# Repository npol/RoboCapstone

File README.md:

# RoboCapstone
An autonomous weed eliminating robot

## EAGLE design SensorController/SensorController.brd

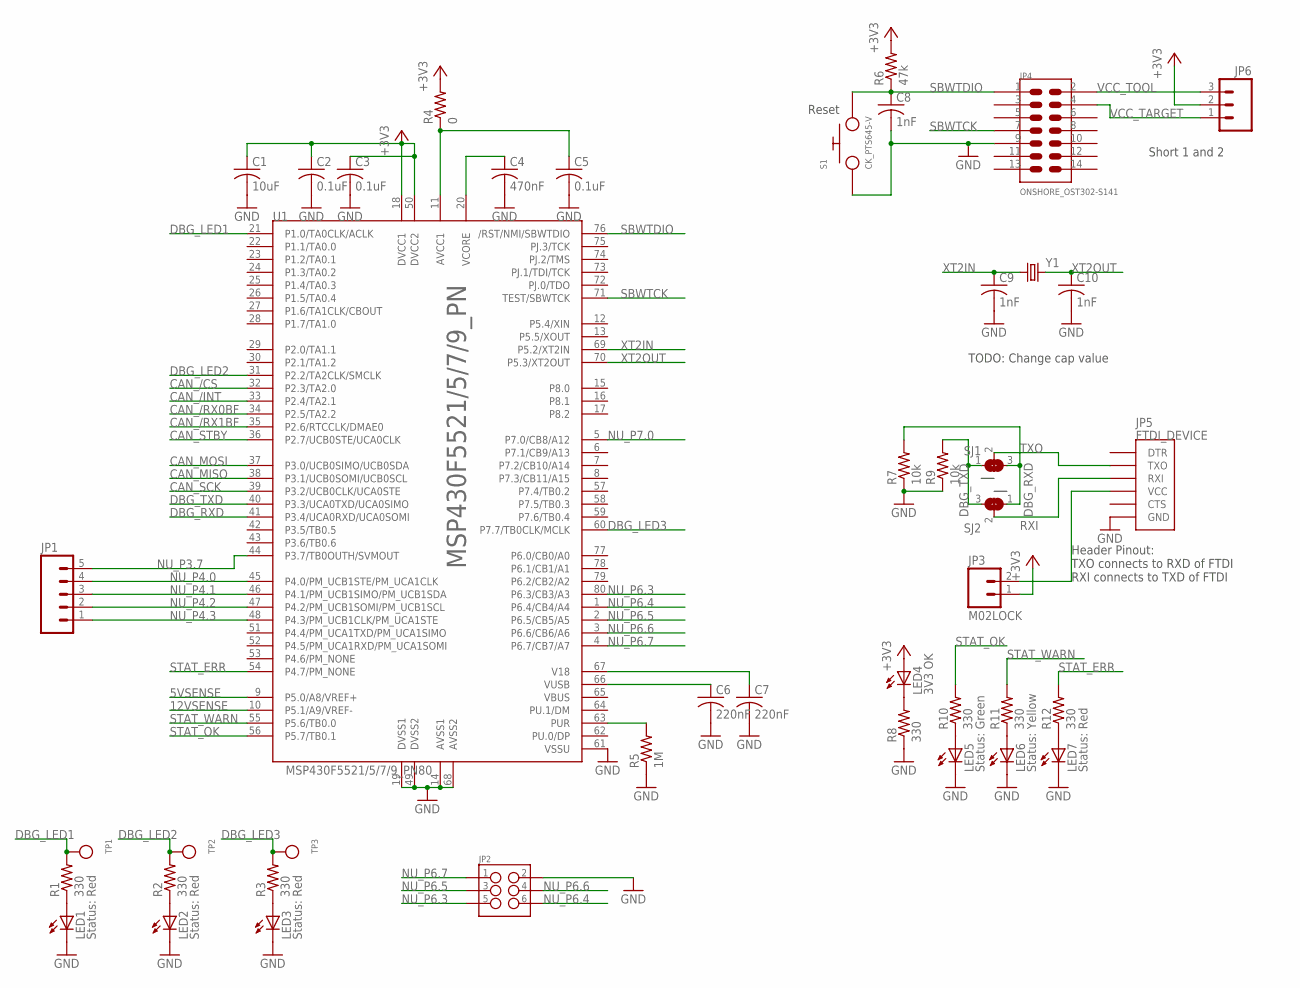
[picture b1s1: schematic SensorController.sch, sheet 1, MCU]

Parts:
C1: 10uF; C0805
C2, C3, C5: 0.1uF; C0603
C4: 470nF; C0603
C6, C7: 220nF; C0603
C8, C9, C10: 1nF; C0603
JP1: M05PTH; 1X05
JP2: M03X22X3_SILK_SM; 2X3
JP3: M02LOCK; 1X02_LOCK
JP4: ONSHORE_OST302-S141
JP5: FTDI_DEVICE; FTDI_DEVICE_SIDE
JP6: M03LOCK; 1X03_LOCK
LED1, LED2, LED3, LED7: Status: Red; LED-0603
LED4: 3V3 OK; LED-0603
LED5: Status: Green; LED-0603
LED6: Status: Yellow; LED-0603
R1, R2, R3, R8, R10, R11, R12: 330; R0603
R4: 0; R0603
R5: 1M; R0603
R6: 47k; R0603
R7, R9: 10k; R0603
S1: CK_PTS645-V
SJ1, SJ2: SOLDERJUMPER_2WAY0603; SOLDERJUMPER_2WAY_OPEN_0603
TP1, TP2, TP3: TESTPOINT0.1"; 1X01_ROUND
U1: MSP430F5521/5/7/9_PN80; PN80
Y1: CRYSTALHC49UV; HC49U-V

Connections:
5VSENSE: U1.9 (P5.0/A8/VREF+); also elsewhere on the board
12VSENSE: U1.10 (P5.1/A9/VREF-); also elsewhere on the board
+3V3: C1.1, C2.1, C3.1, JP3.1, JP6.2, LED4.A, R4.2, R6.2, U1.18 (DVCC1), U1.50 (DVCC2); also elsewhere on the board
AVCC: C5.1, R4.1, U1.11 (AVCC1)
CAN_/CS: U1.32 (P2.3/TA2.0); also elsewhere on the board
CAN_/INT: U1.33 (P2.4/TA2.1); also elsewhere on the board
CAN_/RX0BF: U1.34 (P2.5/TA2.2); also elsewhere on the board
CAN_/RX1BF: U1.35 (P2.6/RTCCLK/DMAE0); also elsewhere on the board
CAN_MISO: U1.38 (P3.1/UCB0SOMI/UCB0SCL); also elsewhere on the board
CAN_MOSI: U1.37 (P3.0/UCB0SIMO/UCB0SDA); also elsewhere on the board
CAN_SCK: U1.39 (P3.2/UCB0CLK/UCA0STE); also elsewhere on the board
CAN_STBY: U1.36 (P2.7/UCB0STE/UCA0CLK); also elsewhere on the board
DBG_LED1: R1.2, TP1.1, U1.21 (P1.0/TA0CLK/ACLK)
DBG_LED2: R2.2, TP2.1, U1.31 (P2.2/TA2CLK/SMCLK)
DBG_LED3: R3.2, TP3.1, U1.60 (P7.7/TB0CLK/MCLK)
DBG_RXD: R7.2, SJ1.3, SJ2.1, U1.41 (P3.4/UCA0RXD/UCA0SOMI)
DBG_TXD: R9.2, SJ1.1, SJ2.3, U1.40 (P3.3/UCA0TXD/UCA0SIMO)
GND: C1.2, C2.2, C3.2, C4.2, C5.2, C6.2, C7.2, C8.2, C9.2, C10.2, JP2.2, JP4.9, JP5.P$6 (GND), LED1.C, LED2.C, LED3.C, LED5.C, LED6.C, LED7.C, R5.1, R7.1, R8.1, R9.1, S1.1, U1.14 (AVSS1), U1.19 (DVSS1), U1.49 (DVSS2), U1.61 (VSSU), U1.68 (AVSS2); also elsewhere on the board
unnamed: JP3.2, JP5.P$4 (VCC)
unnamed: LED4.C, R8.2
unnamed: LED5.A, R10.1
unnamed: LED6.A, R11.1
unnamed: LED7.A, R12.1
unnamed: LED1.A, R1.1
unnamed: R5.2, U1.63 (PUR)
unnamed: LED2.A, R2.1
unnamed: LED3.A, R3.1
NU_P3.7: JP1.5, U1.44 (P3.7/TB0OUTH/SVMOUT)
NU_P4.0: JP1.4, U1.45 (P4.0/PM_UCB1STE/PM_UCA1CLK)
NU_P4.1: JP1.3, U1.46 (P4.1/PM_UCB1SIMO/PM_UCB1SDA)
NU_P4.2: JP1.2, U1.47 (P4.2/PM_UCB1SOMI/PM_UCB1SCL)
NU_P4.3: JP1.1, U1.48 (P4.3/PM_UCB1CLK/PM_UCA1STE)
NU_P6.3: JP2.5, U1.80 (P6.3/CB3/A3)
NU_P6.4: JP2.6, U1.1 (P6.4/CB4/A4)
NU_P6.5: JP2.3, U1.2 (P6.5/CB5/A5)
NU_P6.6: JP2.4, U1.3 (P6.6/CB6/A6)
NU_P6.7: JP2.1, U1.4 (P6.7/CB7/A7)
NU_P7.0: U1.5 (P7.0/CB8/A12)
RXI: JP5.P$3 (RXI), SJ2.2
SBWTCK: JP4.7, U1.71 (TEST/SBWTCK)
SBWTDIO: C8.1, JP4.1, R6.1, S1.2, U1.76 (/RST/NMI/SBWTDIO)
STAT_ERR: R12.2, U1.54 (P4.7/PM_NONE)
STAT_OK: R10.2, U1.56 (P5.7/TB0.1)
STAT_WARN: R11.2, U1.55 (P5.6/TB0.0)
TXO: JP5.P$2 (TXO), SJ1.2
V18: C7.1, U1.67 (V18)
VCC_TARGET: JP4.4, JP6.1
VCC_TOOL: JP4.2, JP6.3
VCORE: C4.1, U1.20 (VCORE)
VUSB: C6.1, U1.66 (VUSB)
XT2IN: C9.1, U1.69 (P5.2/XT2IN), Y1.1
XT2OUT: C10.1, U1.70 (P5.3/XT2OUT), Y1.2

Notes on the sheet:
Short 1 and 2
Reset
TODO: Change cap value
Header Pinout: TXO connects to RXD of FTDI RXI connects to TXD of FTDI

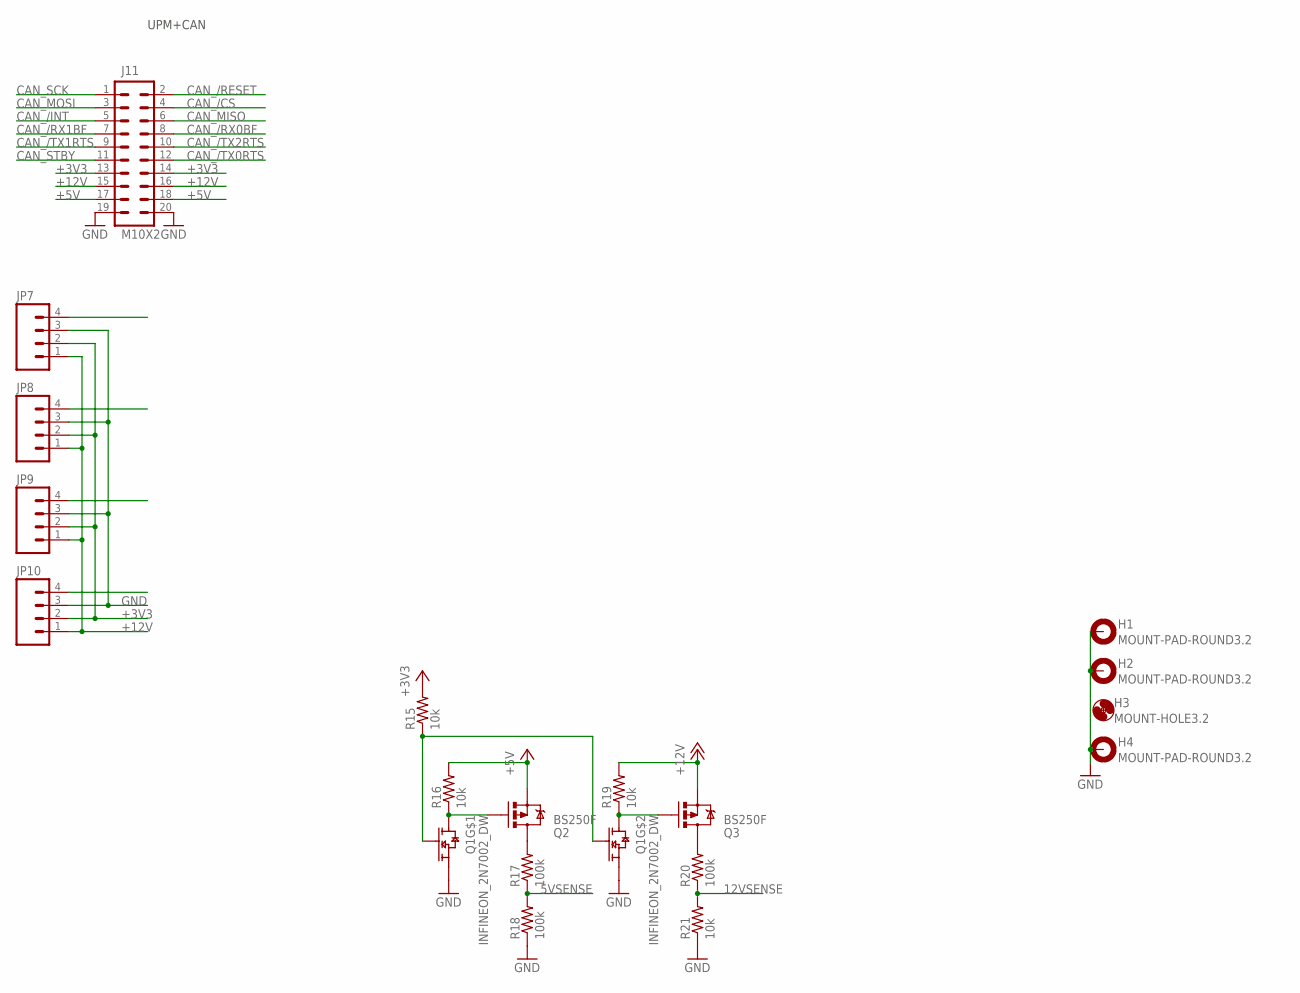
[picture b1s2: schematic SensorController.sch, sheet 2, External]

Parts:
H1, H2, H4: MOUNT-PAD-ROUND3.2; 3,2-PAD
H3: MOUNT-HOLE3.2; 3,2
J11: M10X2; 2X10
JP7, JP8, JP9, JP10: M04PTH; 1X04
Q1: INFINEON_2N7002_DW; INFINEON_SOT363
Q2, Q3: BS250F; SOT23-3
R15, R16, R19, R21: 10k; R0603
R17, R18, R20: 100k; R0603

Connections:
5VSENSE: R17.1, R18.2; also elsewhere on the board
12VSENSE: R20.1, R21.2; also elsewhere on the board
+3V3: J11.13, J11.14, JP7.2, JP8.2, JP9.2, JP10.2, R15.2; also elsewhere on the board
+5V: J11.17, J11.18, Q2.2 (S), R16.2
+12V: J11.15, J11.16, JP7.1, JP8.1, JP9.1, JP10.1, Q3.2 (S), R19.2
CAN_/CS: J11.4; also elsewhere on the board
CAN_/INT: J11.5; also elsewhere on the board
CAN_/RESET: J11.2
CAN_/RX0BF: J11.8; also elsewhere on the board
CAN_/RX1BF: J11.7; also elsewhere on the board
CAN_/TX0RTS: J11.12
CAN_/TX1RTS: J11.9
CAN_/TX2RTS: J11.10
CAN_MISO: J11.6; also elsewhere on the board
CAN_MOSI: J11.3; also elsewhere on the board
CAN_SCK: J11.1; also elsewhere on the board
CAN_STBY: J11.11; also elsewhere on the board
GND: H1.B3,2, H2.B3,2, H4.B3,2, J11.19, J11.20, JP7.3, JP8.3, JP9.3, JP10.3, Q1.1 (SOURCE), Q1.4 (SOURCE), R18.1, R21.1; also elsewhere on the board
unnamed: Q2.3 (D), R17.2
unnamed: Q1.6 (DRAIN), Q2.1 (G), R16.1
unnamed: Q3.3 (D), R20.2
unnamed: Q1.2 (GATE), Q1.5 (GATE), R15.1
VTAP_EN: Q1.3 (DRAIN), Q3.1 (G), R19.1

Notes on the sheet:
UPM+CAN

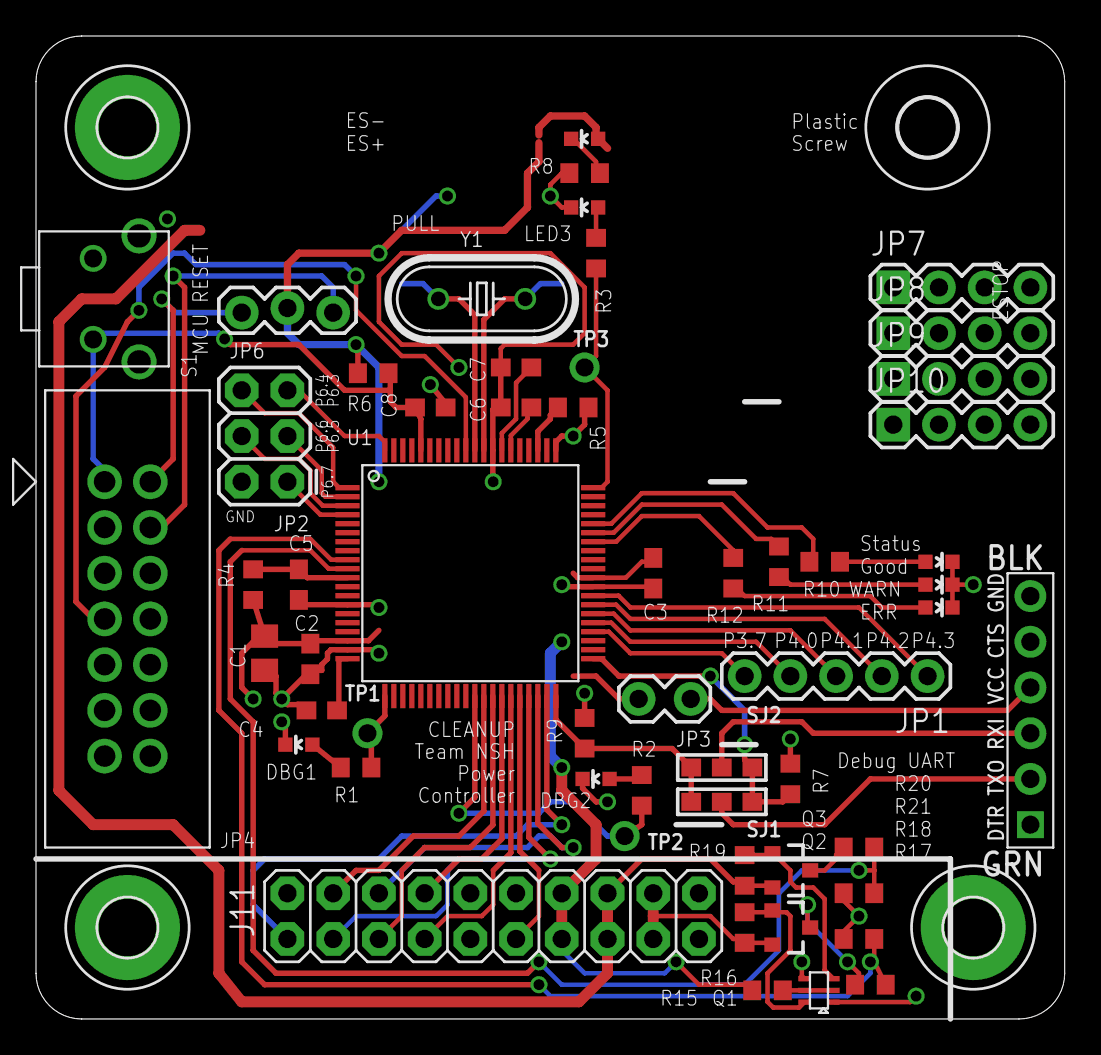
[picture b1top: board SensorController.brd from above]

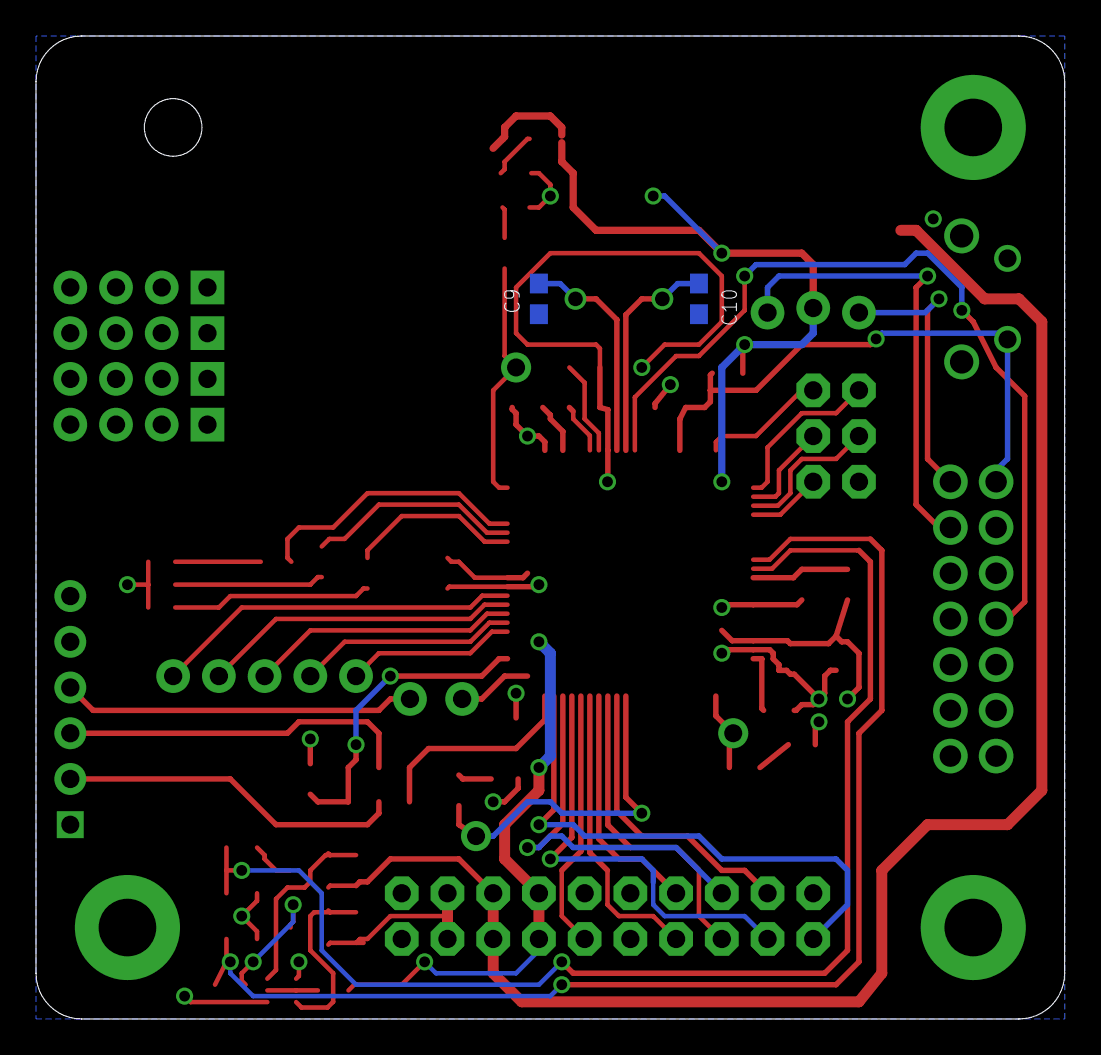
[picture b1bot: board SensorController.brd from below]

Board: 2 copper layers, 57.1 x 54.6 mm, 62 parts (2 on the bottom side), 58 nets.

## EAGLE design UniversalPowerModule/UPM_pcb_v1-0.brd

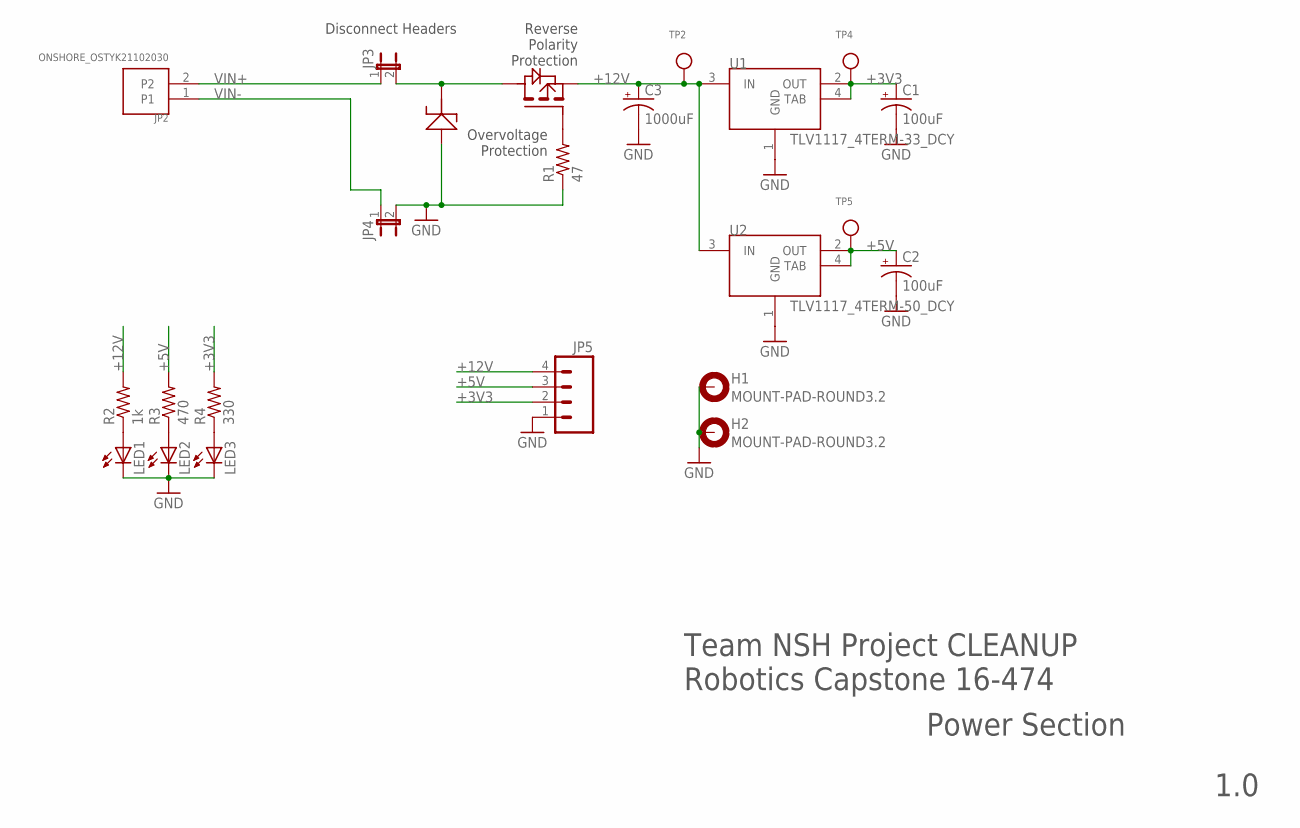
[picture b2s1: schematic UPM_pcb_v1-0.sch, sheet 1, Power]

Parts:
C1, C2: 100uF; E2,5-5
C3: 1000uF; E5-13
D1: VISHAY_SMA6F; VSHY_DO-221AC
H1, H2: MOUNT-PAD-ROUND3.2; 3,2-PAD
JP2: ONSHORE_OSTYK21102030
JP3, JP4: JUMPER2
JP5: M04LOCK; 1X04_LOCK
LED1, LED2, LED3: LED0603; LED-0603
Q1: DMP4047SK3; DIODES_TO252
R1: 47; R0603
R2: 1k; R0603
R3: 470; R0603
R4: 330; R0603
TP2, TP4, TP5: TESTPOINT0.1"; 1X01_ROUND
U1: TLV1117_4TERM-33_DCY; TI_SOT-223_DCY_R-PDSO-G4
U2: TLV1117_4TERM-50_DCY; TI_SOT-223_DCY_R-PDSO-G4

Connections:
+3V3: C1.+, JP5.2, R4.2, TP4.1, U1.2 (OUT), U1.4 (TAB); also elsewhere on the board
+5V: C2.+, JP5.3, R3.2, TP5.1, U2.2 (OUT), U2.4 (TAB); also elsewhere on the board
+12V: C3.+, JP5.4, Q1.2 (S), R2.2, TP2.1, U1.3 (IN), U2.3 (IN); also elsewhere on the board
GND: C1.-, C2.-, C3.-, D1.A, H1.B3,2, H2.B3,2, JP4.2, JP5.1, LED1.C, LED2.C, LED3.C, R1.1, U1.1 (GND), U2.1 (GND); also elsewhere on the board
unnamed: Q1.1 (G), R1.2
unnamed: D1.K, JP3.2, Q1.3 (D)
unnamed: LED1.A, R2.1
unnamed: LED2.A, R3.1
unnamed: LED3.A, R4.1
VIN+: JP2.2, JP3.1
VIN-: JP2.1, JP4.1

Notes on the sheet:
Team NSH Project CLEANUP Robotics Capstone 16-474
1.0
Disconnect Headers
Overvoltage Protection
Reverse Polarity Protection
Power Section

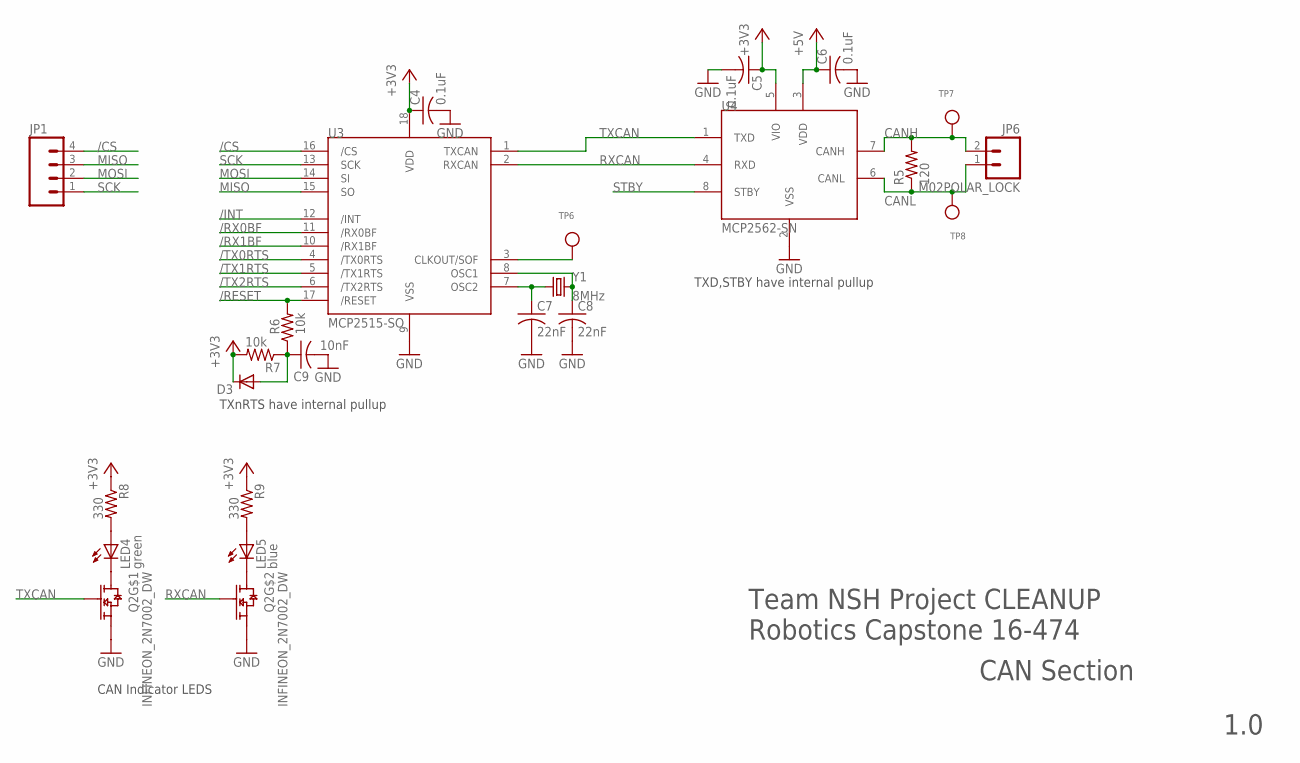
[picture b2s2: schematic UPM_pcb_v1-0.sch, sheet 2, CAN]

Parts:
C4, C5, C6: 0.1uF; C0603
C7, C8: 22nF; C0603
C9: 10nF; C0603
D3: DIODE1N4148; DIODE-1N4148
JP1: M04LOCK; 1X04_LOCK
JP6: M02POLAR_LOCK; MOLEX-1X2_LOCK
LED4: green; LED-0603
LED5: blue; LED-0603
Q2: INFINEON_2N7002_DW; INFINEON_SOT363
R5: 120; R0603
R6, R7: 10k; R0603
R8, R9: 330; R0603
TP6, TP7, TP8: TESTPOINT0.1"; 1X01_ROUND
U3: MCP2515-SO; MCP_SO_SOIC-18
U4: MCP2562-SN; MCP_SN_SOIC-8
Y1: 8MHz; HC49U-V

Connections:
+3V3: C4.1, C5.1, D3.C, R7.2, R8.1, R9.1, U3.18 (VDD), U4.5 (VIO); also elsewhere on the board
+5V: C6.1, U4.3 (VDD); also elsewhere on the board
/CS: JP1.4, U3.16 (/CS); also elsewhere on the board
/INT: U3.12 (/INT); also elsewhere on the board
/RESET: R6.2, U3.17 (/RESET); also elsewhere on the board
/RX0BF: U3.11 (/RX0BF); also elsewhere on the board
/RX1BF: U3.10 (/RX1BF); also elsewhere on the board
/TX0RTS: U3.4 (/TX0RTS); also elsewhere on the board
/TX1RTS: U3.5 (/TX1RTS); also elsewhere on the board
/TX2RTS: U3.6 (/TX2RTS); also elsewhere on the board
CANH: JP6.2, R5.2, TP7.1, U4.7 (CANH)
CANL: JP6.1, R5.1, TP8.1, U4.6 (CANL)
CLKOUT: TP6.1, U3.3 (CLKOUT/SOF)
GND: C4.2, C5.2, C6.2, C7.2, C8.2, C9.2, Q2.1 (SOURCE), Q2.4 (SOURCE), U3.9 (VSS), U4.2 (VSS); also elsewhere on the board
MISO: JP1.3, U3.15 (SO); also elsewhere on the board
MOSI: JP1.2, U3.14 (SI); also elsewhere on the board
unnamed: LED4.C, Q2.6 (DRAIN)
unnamed: C9.1, D3.A, R6.1, R7.1
unnamed: LED5.C, Q2.3 (DRAIN)
unnamed: LED4.A, R8.2
unnamed: LED5.A, R9.2
RXCAN: Q2.5 (GATE), U3.2 (RXCAN), U4.4 (RXD)
SCK: JP1.1, U3.13 (SCK); also elsewhere on the board
STBY: U4.8 (STBY); also elsewhere on the board
TXCAN: Q2.2 (GATE), U3.1 (TXCAN), U4.1 (TXD)
XTAL1: C8.1, U3.8 (OSC1), Y1.2
XTAL2: C7.1, U3.7 (OSC2), Y1.1

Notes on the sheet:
Team NSH Project CLEANUP Robotics Capstone 16-474
1.0
CAN Section
TXD,STBY have internal pullup
TXnRTS have internal pullup
CAN Indicator LEDS

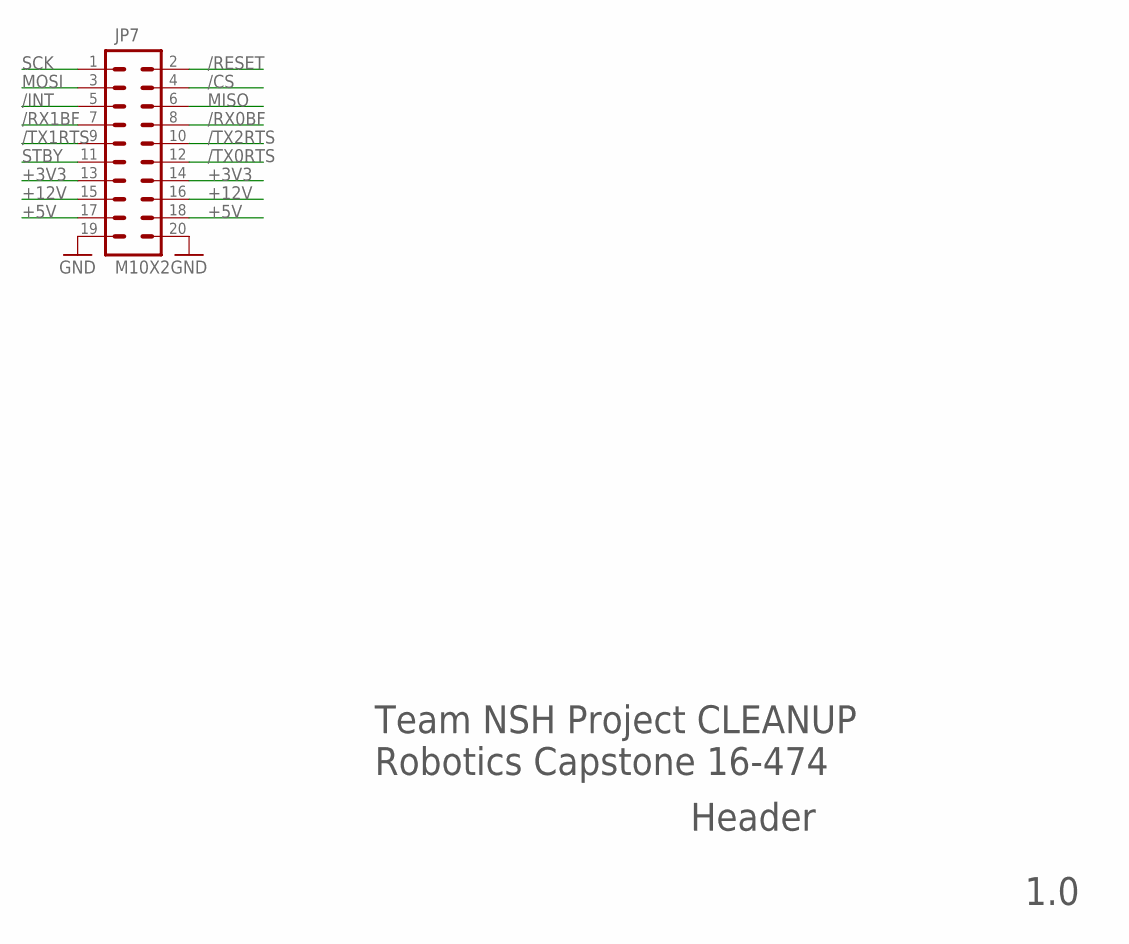
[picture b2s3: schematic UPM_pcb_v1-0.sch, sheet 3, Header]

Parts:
JP7: M10X2; 2X10

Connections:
+3V3: JP7.13, JP7.14; also elsewhere on the board
+5V: JP7.17, JP7.18; also elsewhere on the board
+12V: JP7.15, JP7.16; also elsewhere on the board
/CS: JP7.4; also elsewhere on the board
/INT: JP7.5; also elsewhere on the board
/RESET: JP7.2; also elsewhere on the board
/RX0BF: JP7.8; also elsewhere on the board
/RX1BF: JP7.7; also elsewhere on the board
/TX0RTS: JP7.12; also elsewhere on the board
/TX1RTS: JP7.9; also elsewhere on the board
/TX2RTS: JP7.10; also elsewhere on the board
GND: JP7.19, JP7.20; also elsewhere on the board
MISO: JP7.6; also elsewhere on the board
MOSI: JP7.3; also elsewhere on the board
SCK: JP7.1; also elsewhere on the board
STBY: JP7.11; also elsewhere on the board

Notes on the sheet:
Team NSH Project CLEANUP Robotics Capstone 16-474
1.0
Header

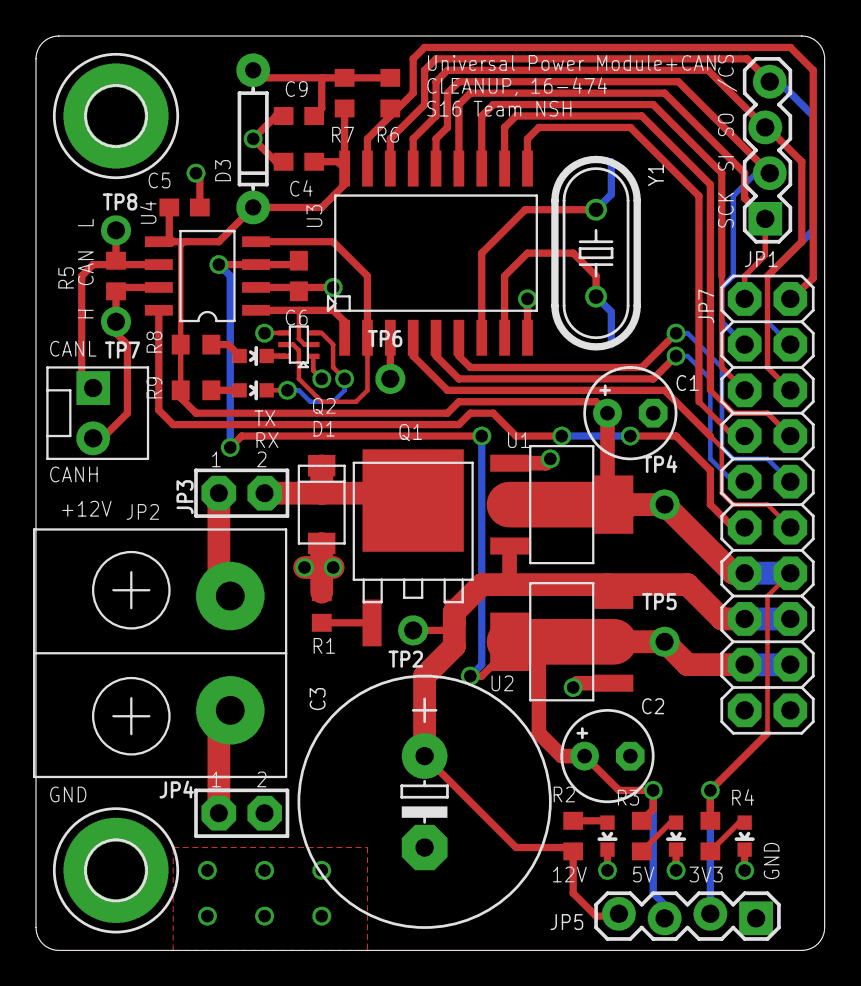
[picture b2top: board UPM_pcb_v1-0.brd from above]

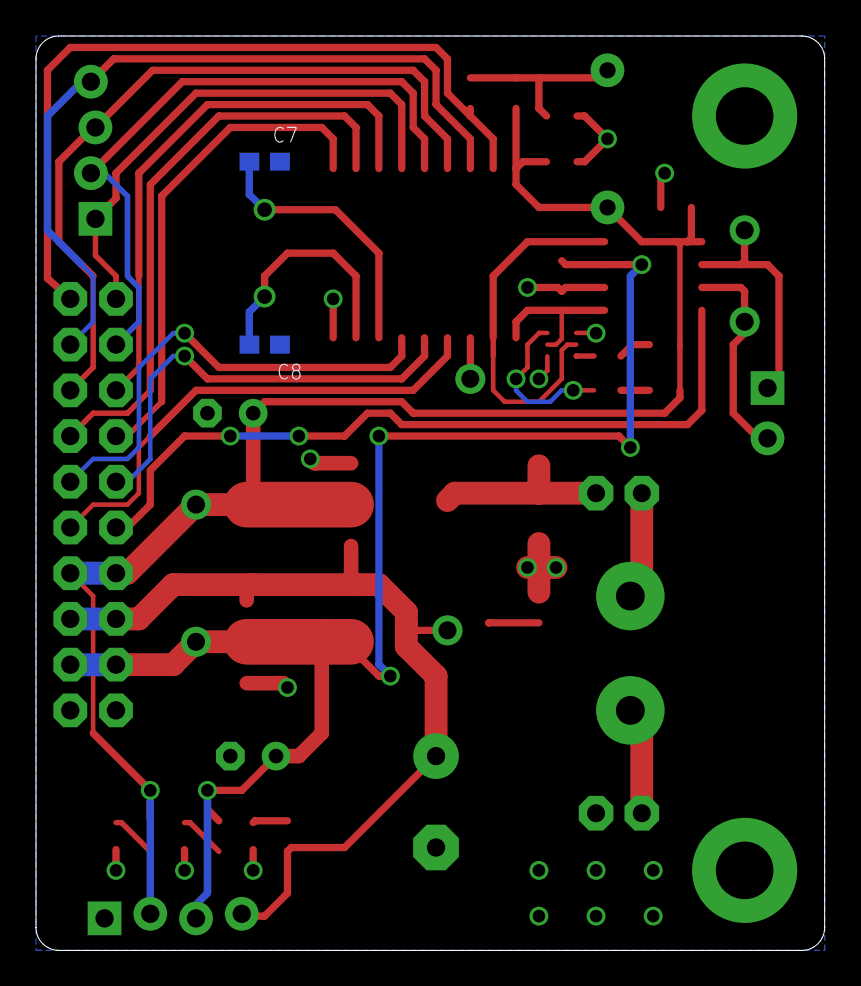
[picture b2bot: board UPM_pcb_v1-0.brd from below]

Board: 2 copper layers, 43.8 x 50.8 mm, 47 parts (2 on the bottom side), 35 nets.

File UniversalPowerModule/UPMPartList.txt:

Partlist

Exported from UPM_pcb_v1-0.sch at 2/22/2016 10:20:48 AM

EAGLE Version 6.6.0 Copyright (c) 1988-2014 CadSoft

Assembly variant: 

Part     Value                 Device                Package                  Library               Sheet

C1       100uF                 CPOL-USE2.5-5         E2,5-5                   rcl                   1
C2       100uF                 CPOL-USE2.5-5         E2,5-5                   rcl                   1
C3       1000uF                CPOL-USE5-13          E5-13                    rcl                   1
C4       0.1uF                 C-USC0603             C0603                    rcl                   2
C5       0.1uF                 C-USC0603             C0603                    rcl                   2
C6       0.1uF                 C-USC0603             C0603                    rcl                   2
C7       22nF                  C-USC0603             C0603                    rcl                   2
C8       22nF                  C-USC0603             C0603                    rcl                   2
C9       10nF                  C-USC0603             C0603                    rcl                   2
D1       VISHAY_SMA6F          VISHAY_SMA6F          VSHY_DO-221AC            npol-discrete         1
D3                             DIODE1N4148           DIODE-1N4148             SparkFun-DiscreteSemi 2
H1       MOUNT-PAD-ROUND3.2    MOUNT-PAD-ROUND3.2    3,2-PAD                  holes                 1
H2       MOUNT-PAD-ROUND3.2    MOUNT-PAD-ROUND3.2    3,2-PAD                  holes                 1
JP1                            M04LOCK               1X04_LOCK                SparkFun-Connectors   2
JP2      ONSHORE_OSTYK21102030 ONSHORE_OSTYK21102030 ONSHORE_OSTYK21102030    npol-connectors       1
JP3                            JUMPER2               JUMPER2                  microbuilder          1
JP4                            JUMPER2               JUMPER2                  microbuilder          1
JP5                            M04LOCK               1X04_LOCK                SparkFun-Connectors   1
JP6      M02POLAR_LOCK         M02POLAR_LOCK         MOLEX-1X2_LOCK           SparkFun-Connectors   2
JP7      M10X2                 M10X2                 2X10                     SparkFun-Connectors   3
LED1                           LED0603               LED-0603                 SparkFun-LED          1
LED2                           LED0603               LED-0603                 SparkFun-LED          1
LED3                           LED0603               LED-0603                 SparkFun-LED          1
LED4     green                 LED0603               LED-0603                 SparkFun-LED          2
LED5     blue                  LED0603               LED-0603                 SparkFun-LED          2
Q1       DMP4047SK3            DMP4047SK3            DIODES_TO252             npol-discrete         1
Q2       INFINEON_2N7002_DW    INFINEON_2N7002_DW    INFINEON_SOT363          npol-discrete         2
R1       47                    R-US_R0603            R0603                    rcl                   1
R2       1k                    R-US_R0603            R0603                    rcl                   1
R3       470                   R-US_R0603            R0603                    rcl                   1
R4       330                   R-US_R0603            R0603                    rcl                   1
R5       120                   R-US_R0603            R0603                    rcl                   2
R6       10k                   R-US_R0603            R0603                    rcl                   2
R7       10k                   R-US_R0603            R0603                    rcl                   2
R8       330                   R-US_R0603            R0603                    rcl                   2
R9       330                   R-US_R0603            R0603                    rcl                   2
TP2                            TESTPOINT0.1"         1X01_ROUND               microbuilder          1
TP4                            TESTPOINT0.1"         1X01_ROUND               microbuilder          1
TP5                            TESTPOINT0.1"         1X01_ROUND               microbuilder          1
TP6                            TESTPOINT0.1"         1X01_ROUND               microbuilder          2
TP7                            TESTPOINT0.1"         1X01_ROUND               microbuilder          2
TP8                            TESTPOINT0.1"         1X01_ROUND               microbuilder          2
U1       TLV1117_4TERM-33_DCY  TLV1117_4TERM-33_DCY  TI_SOT-223_DCY_R-PDSO-G4 npol-power            1
U2       TLV1117_4TERM-50_DCY  TLV1117_4TERM-50_DCY  TI_SOT-223_DCY_R-PDSO-G4 npol-power            1
U3       MCP2515-SO            MCP2515-SO            MCP_SO_SOIC-18           npol-digital          2
U4       MCP2562-SN            MCP2562-SN            MCP_SN_SOIC-8            npol-digital          2
Y1       8MHz                  CRYSTALHC49UV         HC49U-V                  SparkFun-FreqCtrl     2

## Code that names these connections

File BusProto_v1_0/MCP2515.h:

/*
 * MCP2515.h
 *
 *  Created on: Nov 25, 2015
 *      Author: nishant
 */
#include "utils.h"
#include "spi.h"

#ifndef MCP2515_H_
#define MCP2515_H_

uint8_t mcp2515_read_register(uint8_t reg_addr);
void mcp2515_write_register(uint8_t reg_addr, uint8_t data);
void setup_mcp2515(void);
void mcp2562_shutdown_enable(void);
void mcp2562_shutdown_disable(void);
void mcp2515_reset(void);

/* Tx Registers */
//Transmit Buffer Control Registers
#define MCP2515_TXB0CTRL	0x30	//Buffer 0
#define MCP2515_TXB1CTRL	0x40	//Buffer 1
#define MCP2515_TXB2CTRL	0x50	//Buffer 2
#define MCP2515_ABTF		BIT6	//Message Aborted: 1=Message aborted, 0=Transmission successful
#define MCP2515_MLOA		BIT5	//Message Lost Arbitration: 1=Message lost arbitration, 0=Message did not lose arbitration
#define MCP2515_TXERR		BIT4	//Transmission Error Detected: 1=Bus error occurred, 0=No bus error occurred
#define MCP2515_TXREQ		BIT3	//Message Transmit Request: 1=MCU requests transmit, 0=no transmission in progress
#define MCP2515_TXP_0		0x00	//Transmit Priority: Lowest
#define MCP2515_TXP_1		0x01	//Transmit Priority: Medium low
#define MCP2515_TXP_2		0x02	//Transmit Priority: Medium High
#define MCP2515_TXP_3		0x03	//Transmit Priority: High

//TXnRTS pin Control and Status Register
#define MCP2515_TXRTSCTRL	0x0D
#define MCP2515_B2RTS		BIT5	//TX2RTS pin state: reads digital input pin
#define MCP2515_B1RTS		BIT4	//TX1RTS pin state: reads digital input pin
#define MCP2515_B0RTS		BIT3	//TX0RTS pin state: reads digital input pin
#define MCP2515_B2RTSM		BIT2	//TX2RTS pin mode: 1=request transmission of TXB2, 0=digital input
#define MCP2515_B1RTSM		BIT1	//TX1RTS pin mode: 1=request transmission of TXB1, 0=digital input
#define MCP2515_B0RTSM		BIT0	//TX0RTS pin mode: 1=request transmission of TXB0, 0=digital input

//Transmit Buffer Standard Identifier High
#define MCP2515_TXB0SIDH	0x31	//Buffer 0, SID[10:3] in bit[7:0]
#define MCP2515_TXB1SIDH	0x41	//Buffer 1, SID[10:3] in bit[7:0]
#define MCP2515_TXB2SIDH	0x51	//Buffer 2, SID[10:3] in bit[7:0]

//Transmit Buffer Standard Identifier Low
#define MCP2515_TXB0SIDL	0x32	//Buffer 0, SID[2:0] in bit[7:5], EID[17:16] in bit[1:0]
#define MCP2515_TXB1SIDL	0x42	//Buffer 1, SID[2:0] in bit[7:5], EID[17:16] in bit[1:0]
#define MCP2515_TXB2SIDL	0x52	//Buffer 2, SID[2:0] in bit[7:5], EID[17:16] in bit[1:0]
#define MCP2515_TXEXIDE		BIT3	//Extended Identifier Enable: 1=use extended, 0=use standard

//Transmit Buffer Extended Identifier High
#define MCP2515_TXB0EID8	0x33	//Buffer 0, EID[15:8] in bit[7:0]
#define MCP2515_TXB1EID8	0x43	//Buffer 1, EID[15:8] in bit[7:0]
#define MCP2515_TXB2EID8	0x53	//Buffer 2, EID[15:8] in bit[7:0]

//Transmit Buffer Extended Identifier Low
#define MCP2515_TXB0EID0	0x34	//Buffer 0, EID[7:0] in bit[7:0]
#define MCP2515_TXB1EID0	0x44	//Buffer 1, EID[7:0] in bit[7:0]
#define MCP2515_TXB2EID0	0x54	//Buffer 2, EID[7:0] in bit[7:0]

//Transmit Buffer Data Length Code
#define MCP2515_TXB0DLC		0x35	//Buffer 0, DLC[3:0] indicate packet length
#define MCP2515_TXB1DLC		0x45	//Buffer 1, DLC[3:0] indicate packet length
#define MCP2515_TXB2DLC		0x55	//Buffer 2, DLC[3:0] indicate packet length
#define MCP2515_RTR			BIT6	//Remote Transmission Request: 1=Message is Remote frame, 0=Message is data frame

//Transmit Buffer Data Bytes
#define MCP2515_TXB0D0		0x36	//Buffer 0 byte 0
#define MCP2515_TXB0D1		0x37	//Buffer 0 byte 1
#define MCP2515_TXB0D2		0x38	//Buffer 0 byte 2
#define MCP2515_TXB0D3		0x39	//Buffer 0 byte 3
#define MCP2515_TXB0D4		0x3A	//Buffer 0 byte 4
#define MCP2515_TXB0D5		0x3B	//Buffer 0 byte 5
#define MCP2515_TXB0D6		0x3C	//Buffer 0 byte 6
#define MCP2515_TXB0D7		0x3D	//Buffer 0 byte 7

#define MCP2515_TXB1D0		0x46	//Buffer 1 byte 0
#define MCP2515_TXB1D1		0x47	//Buffer 1 byte 1
#define MCP2515_TXB1D2		0x48	//Buffer 1 byte 2
#define MCP2515_TXB1D3		0x49	//Buffer 1 byte 3
#define MCP2515_TXB1D4		0x4A	//Buffer 1 byte 4
#define MCP2515_TXB1D5		0x4B	//Buffer 1 byte 5
#define MCP2515_TXB1D6		0x4C	//Buffer 1 byte 6
#define MCP2515_TXB1D7		0x4D	//Buffer 1 byte 7

#define MCP2515_TXB2D0		0x56	//Buffer 2 byte 0
#define MCP2515_TXB2D1		0x57	//Buffer 2 byte 1
#define MCP2515_TXB2D2		0x58	//Buffer 2 byte 2
#define MCP2515_TXB2D3		0x59	//Buffer 2 byte 3
#define MCP2515_TXB2D4		0x5A	//Buffer 2 byte 4
#define MCP2515_TXB2D5		0x5B	//Buffer 2 byte 5
#define MCP2515_TXB2D6		0x5C	//Buffer 2 byte 6
#define MCP2515_TXB2D7		0x5D	//Buffer 2 byte 7

/* Receive Registers */
#define MCP2515_RXF0SIDH	0x00	//Filter 0 Standard Identifier High, SID[10:3] in bit[7:0]
#define MCP2515_RXF1SIDH	0x04	//Filter 1 Standard Identifier High, SID[10:3] in bit[7:0]
#define MCP2515_RXF2SIDH 	0x08	//Filter 2 Standard Identifier High, SID[10:3] in bit[7:0]
#define MCP2515_RXF3SIDH	0x10	//Filter 3 Standard Identifier High, SID[10:3] in bit[7:0]
#define MCP2515_RXF4SIDH	0x14	//Filter 4 Standard Identifier High, SID[10:3] in bit[7:0]
#define MCP2515_RXF5SIDH	0x18	//Filter 5 Standard Identifier High, SID[10:3] in bit[7:0]

#define MCP2515_RXF0SIDL	0x01	//Filter 0 Standard Identifier Low, SID[2:0] in bit[7:5], EID[17:16] in bit[1:0]
#define MCP2515_RXF1SIDL	0x05	//Filter 1 Standard Identifier Low, SID[2:0] in bit[7:5], EID[17:16] in bit[1:0]
#define MCP2515_RXF2SIDL	0x09	//Filter 2 Standard Identifier Low, SID[2:0] in bit[7:5], EID[17:16] in bit[1:0]
#define MCP2515_RXF3SIDL	0x11	//Filter 3 Standard Identifier Low, SID[2:0] in bit[7:5], EID[17:16] in bit[1:0]
#define MCP2515_RXF4SIDL	0x15	//Filter 4 Standard Identifier Low, SID[2:0] in bit[7:5], EID[17:16] in bit[1:0]
#define MCP2515_RXF5SIDL	0x19	//Filter 5 Standard Identifier Low, SID[2:0] in bit[7:5], EID[17:16] in bit[1:0]
#define MCP2515_RxEXIDE		BIT3	//Extended Identifier Enable, 1=Filter applied to extended, 0=filter applied to standard

#define MCP2515_RXF0EID8	0x02	//Filter 0 Extended Identifier High, EID[15:8] in bit[7:0]
#define MCP2515_RXF1EID8	0x06	//Filter 1 Extended Identifier High, EID[15:8] in bit[7:0]
#define MCP2515_RXF2EID8	0x0A	//Filter 2 Extended Identifier High, EID[15:8] in bit[7:0]
#define MCP2515_RXF3EID8	0x12	//Filter 3 Extended Identifier High, EID[15:8] in bit[7:0]
#define MCP2515_RXF4EID8	0x16	//Filter 4 Extended Identifier High, EID[15:8] in bit[7:0]
#define MCP2515_RXF5EID8	0x1A	//Filter 5 Extended Identifier High, EID[15:8] in bit[7:0]

#define MCP2515_RXF0EID0	0x03	//Filter 0 Extended Identifier Low, EID[7:0] in bit[7:0]
#define MCP2515_RXF1EID0	0x07	//Filter 1 Extended Identifier Low, EID[7:0] in bit[7:0]
#define MCP2515_RXF2EID0	0x0B	//Filter 2 Extended Identifier Low, EID[7:0] in bit[7:0]
#define MCP2515_RXF3EID0	0x13	//Filter 3 Extended Identifier Low, EID[7:0] in bit[7:0]
#define MCP2515_RXF4EID0	0x17	//Filter 4 Extended Identifier Low, EID[7:0] in bit[7:0]
#define MCP2515_RXF5EID0	0x1B	//Filter 5 Extended Identifier Low, EID[7:0] in bit[7:0]

#define MCP2515_RXM0SIDH	0x20	//Mask 0 Standard Identifier High, SID[10:3] in bit[7:0]
#define MCP2515_RXM1SIDH	0x24	//Mask 1 Standard Identifier High, SID[10:3] in bit[7:0]

#define MCP2515_RXM0SIDL	0x21	//Mask 0 Standard Identifier Low, SID[2:0] in bit[7:5], EID[17:16] in bit[1:0]
#define MCP2515_RXM1SIDL	0x25	//Mask 1 Standard Identifier Low, SID[2:0] in bit[7:5], EID[17:16] in bit[1:0]

#define MCP2515_RXM0EID8	0x22	//Mask 0 Extended Identifier High, EID[15:8] in bit[7:0]
#define MCP2515_RXM1EID8	0x26	//Mask 1 Extended Identifier High, EID[15:8] in bit[7:0]

#define MCP2515_RXM0EID0	0x23	//Mask 0 Extended Identifier Low, EID[7:0] in bit[7:0]
#define MCP2515_RXM1EID0	0x27	//Mask 1 Extended Identifier Low, EID[7:0] in bit[7:0]

/* Configuration Registers: Timing */
#define MCP2515_CNF1		0x2A	//Configuration 1
#define MCP2515_SJW_0		0x00	//Synchronization Jump Width: 1xTQ
#define MCP2515_SJW_1		0x40	//Synchronization Jump Width: 2xTQ
#define MCP2515_SJW_2		0x80	//Synchronization Jump Width: 3xTQ
#define MCP2515_SJW_3		0xC0	//Synchronization Jump Width: 4xTQ
//BRP[5:0] in bit[5:0]: Baud rate prescaler

#define MCP2515_CNF2		0x29	//Configuration 2
#define MCP2515_BTLMODE		BIT7	//PS2 Bit Time Length
#define MCP2515_SAM			BIT6	//Sample Point Configuration
//PHSEG1[2:0] in bit[5:3]: PS1 Length bits
//PRSEG[2:0] in bit[2:0]: Propagation Segment Length bits

#define MCP2515_CNF3		0x28	//Configuration 3
#define MCP2515_SOF			BIT7	//Start of Frame Signal
#define MCP2515_WAKFIL		BIT6	//Wakeup filter enable
//PHSEG2[2:0] in bit[2:0]: PS2 Length bits

/* Error Indication Registers */


#endif /* MCP2515_H_ */

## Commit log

2016-02-08 Initial commit, with UPM
2016-02-08 Initial commit: port from old untracked firmware folder
2016-02-09 UART Tx working, sending string continuously, tested
2016-02-09 Terminal prompt working (actually)
2016-02-11 Added debug commands for LED and buttons, tested
2016-02-11 Added mcp2515 manual register commands to debug interface
2016-02-12 Magic school bus working, bus proto tested with 3 boards
2016-02-14 PC interface compliant, sometimes locks up
2016-02-14 Lockup seems to be fixed by changing flashing from 4 leds to 3 leds
2016-02-16 UPM+CAN v1 sent to FAB
2016-02-19 Relay on PCB design, before revising to socket relays
2016-02-21 Mostly done, but brd file is blank
2016-02-21 Mostly done, now correct brd file
2016-02-21 Mob/Elim controller ready for fab
2016-02-21 Created PCCAN and Power controller from Mobility-Elim controller
2016-02-21 Removed irrelevant circuits for PC2CAN and Power Controller
2016-02-22 Power Controller ready for fab
2016-02-22 PC2CAN ready for fab
2016-02-22 Power Controller, Elim-Mobility Controller, and PC2CAN sent to FAB
2016-02-23 Tested bus proto, added joystick python code from USAR
2016-02-24 modified joystick python code to match msp baudrate
2016-02-25 Created debug projects for msp430f5529
2016-02-25 tested joystick, works, but without drivetrain, for clock, outputs 5MHz with 4MHz crystal
2016-02-28 Roboclaw joystick code tested, some packet errors or drops but okay for testing
2016-02-28 Clocking working on launchpad, SMCLK not outputting to P2.2, but could be b/c no module uses it
2016-02-28 Added UNMI handler
2016-02-29 Debug UART Tx tested
2016-02-29 Debug channel working
2016-03-01 Add parts lists, boundary controller
2016-03-12 Encoder schematic done, Sensor Controller created from PowerController
2016-03-12 Deleted irrelevant parts from SensorController
2016-03-17 25MHz clock working, used for bringup tests
2016-03-17 Created Mobility-Elim controller project
2016-03-17 Added roboclaw packet gen functions, untested
2016-03-17 Tested debug uart on mobility controller
2016-03-18 Ported uscia0 debug code to uscia1 roboclaw uart driver in Mobility Controller
2016-03-21 Working drivers for mobility-elim
2016-03-25 Mobility: Added error reporting and roboclaw state machine
2016-03-25 Tested error/warning reporting
2016-03-27 Working and tested error recording and printing
2016-03-27 Tested running roboclaw motors through debug channel
2016-03-27 Added roboclaw and adc monitoring, untested
2016-03-27 Tested on robot, working error handling and encoder polling. Get about 30Hz encoder, 10s check interval
2016-03-29 Tested: new string compare function, persistent commands, on robot
2016-04-07 Wrote Drill state machine, untested
2016-04-08 Tested drill code on HW, with LEDs
2016-04-08 Stepper tested with HW and stepper
2016-04-10 Wrote stepper SM code, untested
2016-04-13 Changed stepper to run multiple pulses, fixed roboclaw hang
2016-04-13 No warnings generated on startup
2016-04-14 Wrote roboclaw velocity control commands
2016-04-14 Tested PID read commands on drivetrain, fixed rx buffer fillup issue
2016-04-15 Working with hardware: velocity control
2016-04-16 Created Sensor Controller FW, added ADC from Mechatronics
2016-04-16 Added CAN for sensor controller
2016-04-17 Tested sensor controller on hardware. ADC and can spi works
2016-04-17 Wrote CAN SM for sensor controller
2016-04-21 Sensor Controller CAN working
2016-04-22 Tested PC UART for PC2CAN
2016-04-22 Added acceleration to Mobility-Elim
2016-04-22 Fixed CAN SPI rx overrun bug for Sensor Controller, tested on HW
2016-04-23 Added and tested CAN between Mobility-Elim and PC2CAN
2016-04-23 Snapshot of CAN debugging: Message is sent correctly, but recieve buffer is consistently wrong
2016-04-23 Changed mobility controller to use USB as PC interface instead of CAN
2016-04-23 Tested new pc interface with mobility controller only, updated python script to set fixed value for motor speeds DO NOT RUN WITH ROBOCLAWgit add -Aabcd+efgh
2016-04-23 Added long to byte conversion
2016-04-23 Working joystick to Mobility PC interface
2016-04-24 Wrote code for ESTOP, CRC error checking
2016-04-24 Tested ESTOP and CRC checking in HW
2016-04-26 Stepper and drill work with debug commands
2016-04-28 Stepper now goes to wait instead of wait home
2016-05-12 Final demo code

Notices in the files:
parts and their libraries:
SparkFun-Connectors: Licensing: CC v3.0 Share-Alike You are welcome to use this library for commercial purposes.
microbuilder: This work is placed in the public domain, and may be freely used for commercial and non-commercial work with the following conditions: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
